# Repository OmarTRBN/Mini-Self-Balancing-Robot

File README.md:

# Self Balancing Robot

A small and cheap self balancing robot that uses a kalman filter and PID control.

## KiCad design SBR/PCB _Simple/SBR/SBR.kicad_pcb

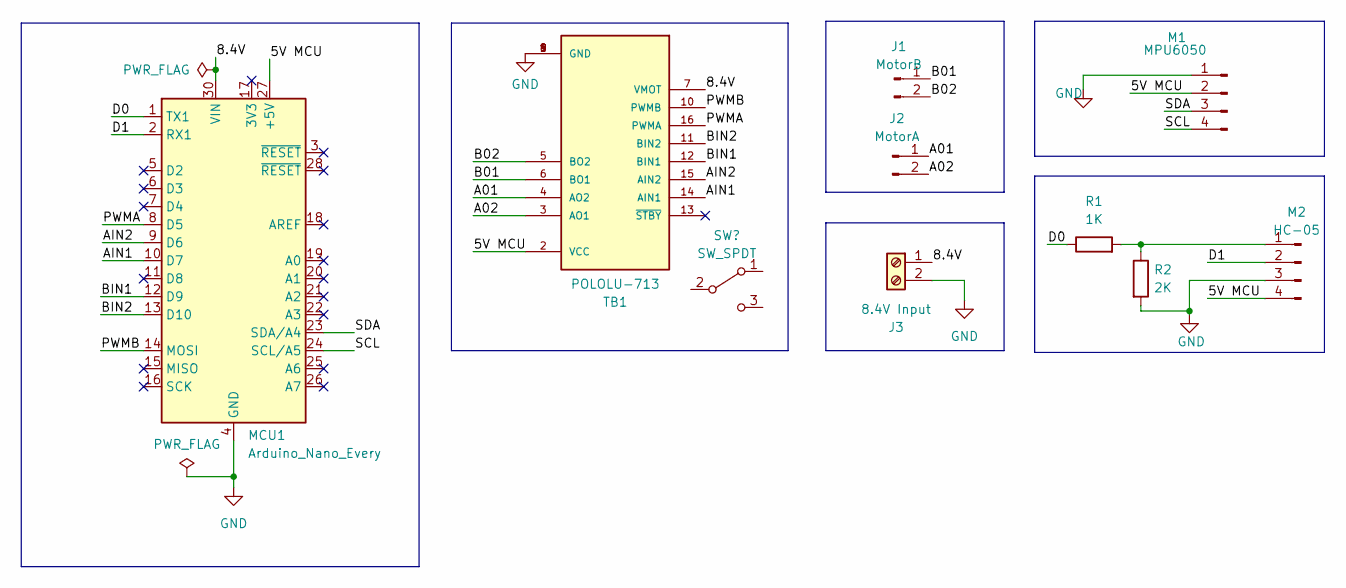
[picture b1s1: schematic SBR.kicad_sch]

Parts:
J1: MotorB; PinHeader_1x02_P2.54mm_Vertical
J2: MotorA; PinHeader_1x02_P2.54mm_Vertical
J3: 8.4V Input; TerminalBlock_RND_205-00001_1x02_P5.00mm_Horizontal
M1: MPU6050; PinHeader_1x04_P2.54mm_Vertical
M2: HC-05; PinHeader_1x04_P2.54mm_Vertical
MCU1: Arduino_Nano_Every; Arduino_Nano
R1: 1K; R_Axial_DIN0207_L6.3mm_D2.5mm_P7.62mm_Horizontal
R2: 2K; R_Axial_DIN0207_L6.3mm_D2.5mm_P7.62mm_Horizontal
TB1: POLOLU-713; SHIELD_POLOLU-713

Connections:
/5V MCU: M1.2, M2.4, MCU1.27 (+5V), TB1.2 (VCC)
/8.4V: J3.1, MCU1.30 (VIN), TB1.7 (VMOT)
/A01: J2.1, TB1.4 (AO2)
/A02: J2.2, TB1.3 (AO1)
/AIN1: MCU1.10 (D7), TB1.14 (AIN1)
/AIN2: MCU1.9 (D6), TB1.15 (AIN2)
/B01: J1.1, TB1.6 (BO1)
/B02: J1.2, TB1.5 (BO2)
/BIN1: MCU1.12 (D9), TB1.12 (BIN1)
/BIN2: MCU1.13 (D10), TB1.11 (BIN2)
/D0: MCU1.1 (TX1), R1.1
/D1: M2.2, MCU1.2 (RX1)
/PWMA: MCU1.8 (D5), TB1.16 (PWMA)
/PWMB: MCU1.14 (MOSI), TB1.10 (PWMB)
/SCL: M1.4, MCU1.24 (SCL/A5)
/SDA: M1.3, MCU1.23 (SDA/A4)
GND: J3.2, M1.1, M2.3, MCU1.4 (GND), MCU1.29 (GND), R2.2, TB1.1 (GND), TB1.8 (GND), TB1.9 (GND)
unnamed: M2.1, R1.2, R2.1

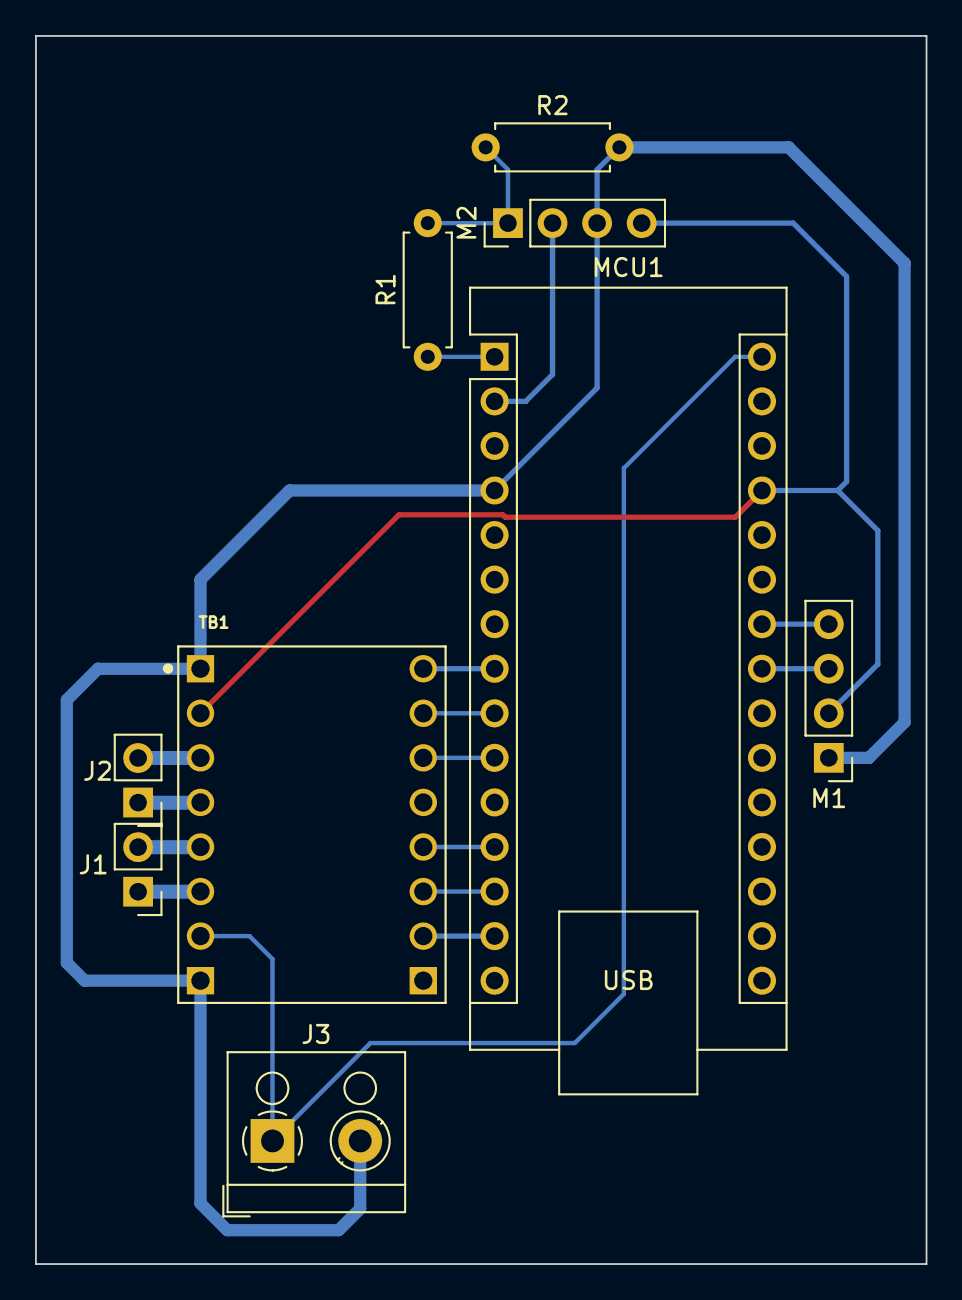
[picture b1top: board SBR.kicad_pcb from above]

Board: 2 copper layers, 50.8 x 70.0 mm, 9 parts (0 on the bottom side), 18 nets.

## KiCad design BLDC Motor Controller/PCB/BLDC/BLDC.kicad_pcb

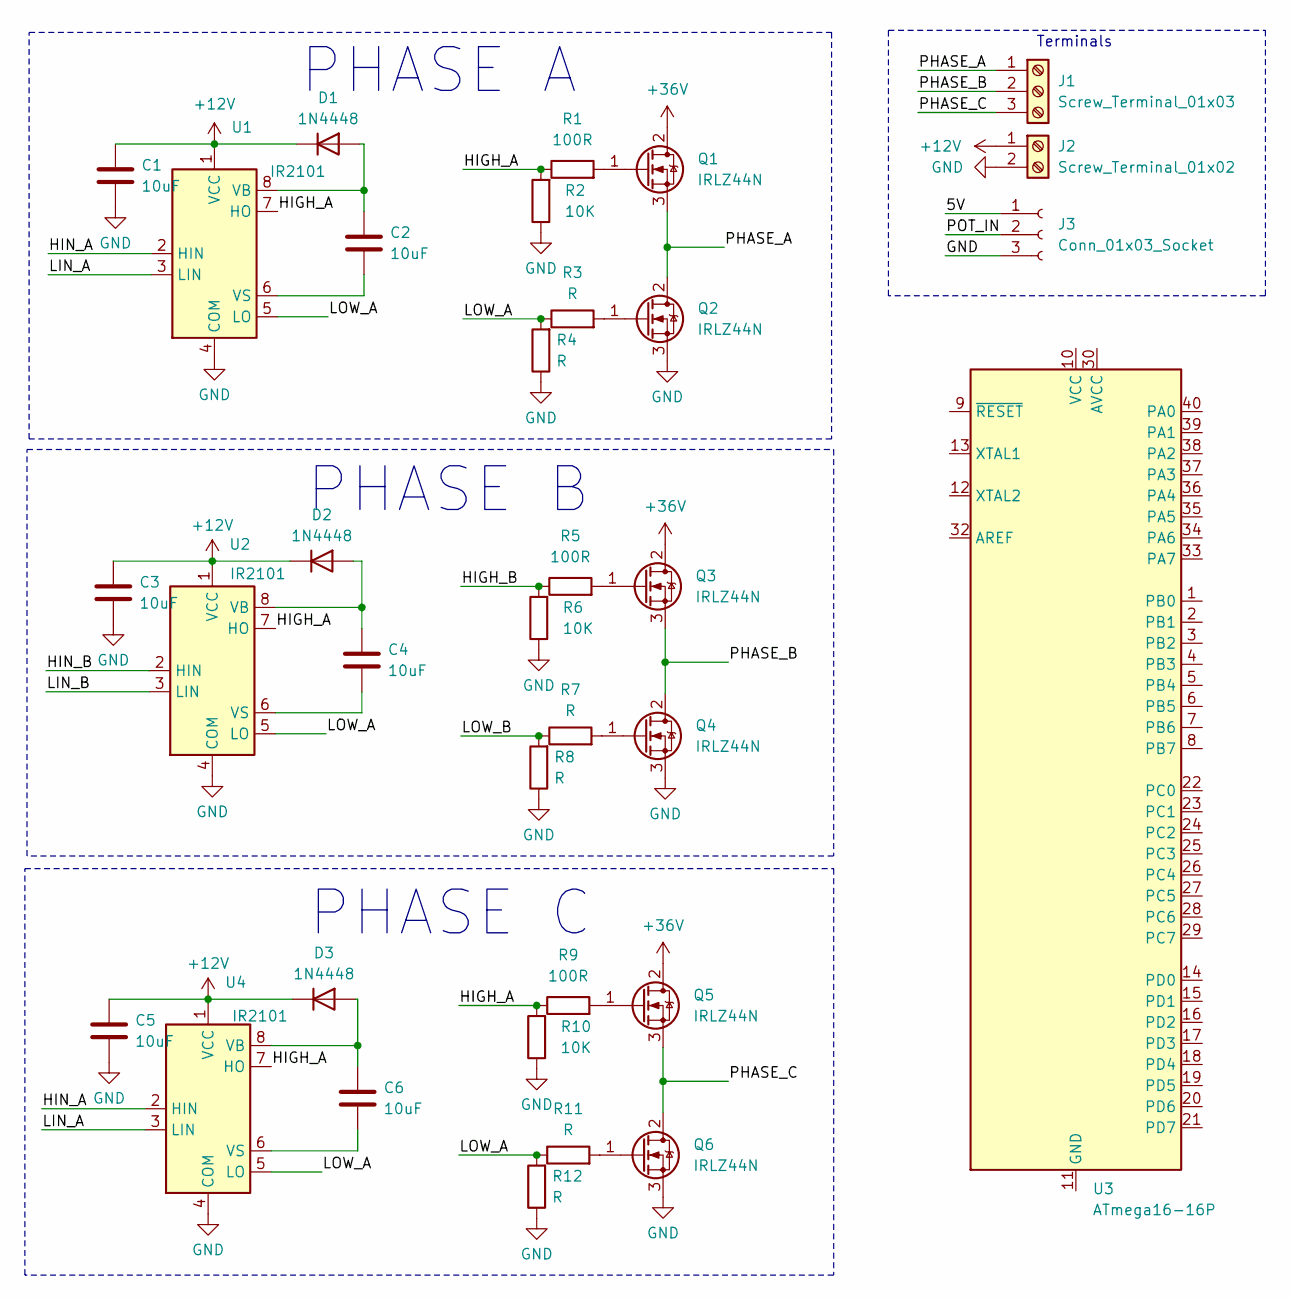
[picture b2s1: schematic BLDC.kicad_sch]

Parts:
C1, C3, C5: 10uF; C_Disc_D5.1mm_W3.2mm_P5.00mm
C2, C4, C6: 10uF; C_Radial_D6.3mm_H5.0mm_P2.50mm
D1, D2, D3: 1N4448; D_DO-35_SOD27_P7.62mm_Horizontal
J1: Screw_Terminal_01x03; TerminalBlock_MetzConnect_Type101_RT01603HBWC_1x03_P5.08mm_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
J2: Screw_Terminal_01x02; TerminalBlock_MetzConnect_Type101_RT01602HBWC_1x02_P5.08mm_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
J3: Conn_01x03_Socket; PinHeader_1x03_P2.54mm_Vertical
Q1, Q2, Q3, Q4, Q5, Q6: IRLZ44N; TO-220-3_Horizontal_TabUp
R1, R5, R9: 100R; R_Axial_DIN0204_L3.6mm_D1.6mm_P5.08mm_Horizontal
R2, R6, R10: 10K; R_Axial_DIN0204_L3.6mm_D1.6mm_P5.08mm_Horizontal
R3, R4, R7, R8, R11, R12: R; R_Axial_DIN0204_L3.6mm_D1.6mm_P5.08mm_Horizontal
U1, U2, U4: IR2101; DIP-8_W7.62mm
U3: ATmega16-16P; DIP-40_W15.24mm

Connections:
+12V: C1.1, C3.1, C5.1, D1.1 (K), D2.1 (K), D3.1 (K), J2.1, U1.1 (VCC), U2.1 (VCC), U4.1 (VCC)
+36V: Q1.2 (D), Q3.2 (D), Q5.2 (D)
/5V: J3.1
/HIGH_A: R1.1, R2.2, R9.1, R10.2, U1.7 (HO), U2.7 (HO), U4.7 (HO)
/HIGH_B: R5.1, R6.2
/HIN_A: U1.2 (HIN), U4.2 (HIN)
/HIN_B: U2.2 (HIN)
/LIN_A: U1.3 (LIN), U4.3 (LIN)
/LIN_B: U2.3 (LIN)
/LOW_A: R3.1, R4.2, R11.1, R12.2, U1.5 (LO), U2.5 (LO), U4.5 (LO)
/LOW_B: R7.1, R8.2
/PHASE_A: J1.1, Q1.3 (S), Q2.2 (D)
/PHASE_B: J1.2, Q3.3 (S), Q4.2 (D)
/PHASE_C: J1.3, Q5.3 (S), Q6.2 (D)
/POT_IN: J3.2
GND: C1.2, C3.2, C5.2, J2.2, J3.3, Q2.3 (S), Q4.3 (S), Q6.3 (S), R2.1, R4.1, R6.1, R8.1, R10.1, R12.1, U1.4 (COM), U2.4 (COM), U4.4 (COM)
unnamed: C2.1, D1.2 (A), U1.8 (VB)
unnamed: C4.1, D2.2 (A), U2.8 (VB)
unnamed: C6.1, D3.2 (A), U4.8 (VB)
unnamed: Q1.1 (G), R1.2
unnamed: Q2.1 (G), R3.2
unnamed: Q3.1 (G), R5.2
unnamed: Q4.1 (G), R7.2
unnamed: Q5.1 (G), R9.2
unnamed: Q6.1 (G), R11.2
unnamed: C2.2, U1.6 (VS)
unnamed: C4.2, U2.6 (VS)
unnamed: U3.11 (GND), U3.31 (GND)
unnamed: C6.2, U4.6 (VS)

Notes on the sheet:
PHASE C
Terminals
PHASE A
PHASE B

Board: 2 copper layers, 34 parts (0 on the bottom side), 25 nets, no tracks yet.

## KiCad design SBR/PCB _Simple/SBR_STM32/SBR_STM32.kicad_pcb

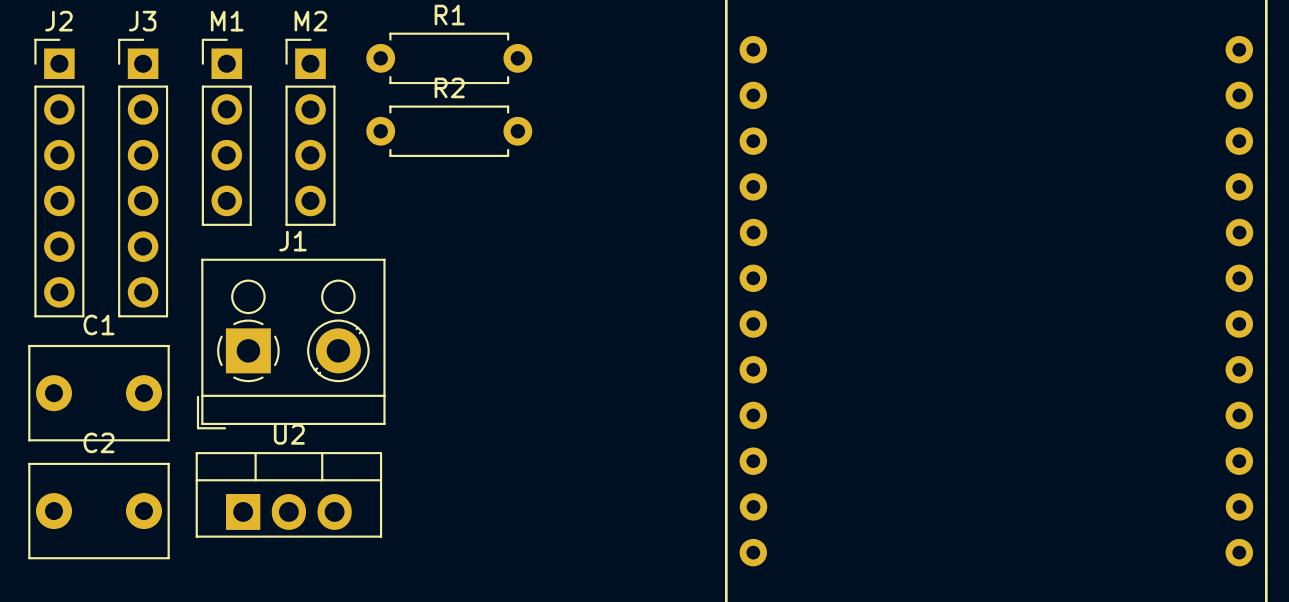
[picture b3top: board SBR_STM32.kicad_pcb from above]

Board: 2 copper layers, 11 parts (0 on the bottom side), 13 nets, no tracks yet.

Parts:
C1: 0.33uF; C_Disc_D7.5mm_W5.0mm_P5.00mm
C2: 0.1uF; C_Disc_D7.5mm_W5.0mm_P5.00mm
J1: 12V Input; TerminalBlock_RND_205-00001_1x02_P5.00mm_Horizontal
J2: MOTOR_A; PinHeader_1x06_P2.54mm_Vertical
J3: MOTOR_B; PinHeader_1x06_P2.54mm_Vertical
M1: MPU6050; PinHeader_1x04_P2.54mm_Vertical
M2: HC-05; PinHeader_1x04_P2.54mm_Vertical
R1: 1K; R_Axial_DIN0207_L6.3mm_D2.5mm_P7.62mm_Horizontal
R2: 2K; R_Axial_DIN0207_L6.3mm_D2.5mm_P7.62mm_Horizontal
U1: STM32F030F4P6
U2: LM7805; TO-220-3_Vertical

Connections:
/5V MCU: J2.4, J3.4, M1.1, M2.4, U1.13 (5V)
/5V REG: C2.1, U1.8 (VDDA), U2.3 (VO)
/12V: C1.1, J1.2, U2.1 (VI)
/D0: R1.1, U1.11 (PF0)
/D1: M2.2, U1.10 (PF1)
/MA_ENCA: J2.5, U1.21 (PA6)
/MA_ENCB: J2.6, U1.20 (PA7)
/MB_ENCA: J3.5, U1.18 (PA9)
/MB_ENCB: J3.6, U1.17 (PA10)
/SCL: M1.4, U1.15 (PA14)
/SDA: M1.3, U1.16 (PA13)
GND: C1.2, C2.2, J1.1, J2.3, J3.3, M1.2, M2.3, R2.2, U1.1 (GND), U1.2 (GND), U2.2 (GND)
unnamed: M2.1, R1.2, R2.1

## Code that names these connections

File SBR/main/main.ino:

#include <Wire.h>
#include "mpu.h"
#include "KalmanFilter.h"

// Motors
#define PWMB 11
#define BIN2 10
#define BIN1 9
#define PWMA 5
#define AIN2 6
#define AIN1 7
#define STBY 8

// MPU 
float accX, accY, accZ;
float gyroX, gyroY, gyroZ;
float accPitch = 0;
float accRoll = 0;

// Kalman Filter
//double Q_a_pitch=0.001, Q_b_pitch=0.003, R_pitch=0.05;
//KalmanFilter2D kalmanPitch(Q_a_pitch, Q_b_pitch, R_pitch);
//double kalPitch = 0; 
double Q_a_roll=0.001, Q_b_roll=0.003, R_roll=0.02; 
KalmanFilter2D kalmanRoll(Q_a_roll, Q_b_roll, R_roll);
double kalRoll = 0;

// PID Controller
float pidError=0.0, prevPidError=0.0, prevPrevPidError=0.0, integral=0.0, derivative=0.0;
const float Kp=27.5, Ki=315.3, Kd=0.7;
unsigned long pidTimeNow=0, pidTimePrev=0; float deltaT=0.0;
int outputPID=0;

void setup() 
{
  pinMode(PWMB, OUTPUT);
  pinMode(BIN2, OUTPUT);
  pinMode(BIN1, OUTPUT);
  pinMode(PWMA, OUTPUT);
  pinMode(AIN2, OUTPUT);
  pinMode(AIN1, OUTPUT);
  pinMode(STBY, OUTPUT);

  digitalWrite(STBY, HIGH);
  Serial.begin(9600);

  // Initialize MPU6050
  initMpu();
}

void loop()
{
  getValues(&accX, &accY, &accZ, &gyroX, &gyroY, &gyroZ);
  
  // Calculate Pitch & Roll from accelerometer (deg)
  //  accPitch = (double) atan( (double)-accX / (double)sqrt(accY*accY + accZ*accZ) ) * 180.0/3.141593;
  accRoll  = (double) atan( (double)accY / sqrt(accX*accX + accZ*accZ) ) * 180.0/3.141593;

  // Kalman filter
  //  kalPitch = kalmanPitch.estimate(accPitch, gyroY);
  kalRoll = kalmanRoll.estimate(accRoll, gyroX);
  
  // PID Controller
  pidTimeNow = micros();
  deltaT = (float)(pidTimeNow-pidTimePrev)/1.0e6;

  pidError = -2.50 - (float)kalRoll; // Proportional term
  integral += pidError*deltaT; // Integral term
  derivative = (float)(3*pidError-4*prevPidError+prevPrevPidError)/(2.0*deltaT); // Derivative term
  outputPID = (int) (Kp*pidError + Ki*integral + Kd*derivative);

  // Processing the PID output
  proccesOutput();
  analogWrite(PWMA, outputPID);
  analogWrite(PWMB, outputPID);
  prevPidError = pidError;
  prevPrevPidError = prevPidError;
  pidTimePrev=pidTimeNow;

  // Sending data
//  Serial.print("Control Input: ");
//  Serial.print(outputPID);
  Serial.print(", Kalman roll angle: ");
  Serial.println(kalRoll);
//  Serial.print(", Kalman pitch angle: ");
//  Serial.println(kalPitch);
}

void proccesOutput()
{
  if (outputPID>0)
  {
    moveForward();
    if (outputPID>255)
    {
      outputPID=255;
    }
  }
  else
  {
    outputPID=-outputPID;
    moveBackward();
    if (outputPID>255)
    {
      outputPID=255;
    }
  }
}

void moveForward()
{
  digitalWrite(AIN1, 1);
  digitalWrite(AIN2, 0);
  digitalWrite(BIN1, 0);
  digitalWrite(BIN2, 1);
}

void moveBackward()
{
  digitalWrite(AIN1, 0);
  digitalWrite(AIN2, 1);
  digitalWrite(BIN1, 1);
  digitalWrite(BIN2, 0);
}

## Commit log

2024-05-18 First commit.
2024-05-23 Added copper fill to PCB, and made small design changes.
2024-05-26 Added robotic arm CAD files.
2024-06-13 Added Kalman Filter for MPU6050.
2024-06-18 Added Data Logging folder to test out Kalman Filter in MATLAB.
2024-06-18 Removed Ref/ folder.
2024-06-19 Designed case for Li-Po batteries.
2024-06-28 Added Kalman Filter class.
2024-06-29 Modified main code.
2024-06-29 Modified PID controller to use a more accurate derivative.
2024-07-03 Tuned PID values.
2024-07-31 Organized files and tuned PID parameters.
2024-07-31 Added .step file for CAD assembly.
